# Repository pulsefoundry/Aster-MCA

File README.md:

# Aster MCA

[简体中文](README.zh-CN.md)

Aster MCA is a compact, USB-powered 4096-channel pulse-height analyzer for
already-amplified detector signals. It combines a 12-bit 10 MSPS ADC, a Gowin
GW1N-4 FPGA, and a CH347T USB/JTAG/UART bridge on one 90 mm × 70 mm four-layer
board.

> **Prototype status:** revision 0.1 has acquired a repeatable Cs-137 spectrum
> from an amplified NaI(Tl)/PMT probe, but the published as-built hardware has
> three mandatory assembly notes. Do not order or assemble the v0.1 production
> package unchanged. See [Hardware errata](docs/hardware-errata-v0.1.md).

*Assembled and physically validated v0.1 prototype.*

## What works

- ADC12010 parallel capture at 10 MSPS.
- FPGA baseline tracking, threshold detection, peak-height extraction, pulse
  rejection, saturation recovery, and a 4096 × 32-bit histogram.
- USB communication on macOS through the on-board CH347T and libusb; no serial
  driver or external programmer is required.
- Volatile SRAM configuration over the same USB-C connector.
- Live diagnostics for ADC min/max/baseline, triggers, accepted/rejected and
  saturated events, histogram drops, live samples, and UART errors.
- Repeatable source-versus-background separation on the first repaired boards.

The current physically validated firmware is **v1.9**. It keeps the proven v1.3
MCA algorithm but moves all 12 ADC inputs into dedicated falling-edge IOLOGIC
registers, followed by a full-cycle fabric pipeline stage. Two independently
placed images now produce matching Cs-137 spectra. FPGA configuration is
volatile and must be reloaded after power loss.

## Aster MCA v2.0 concept

The repository also contains a routed, explicitly unreleased
[v2.0 high-performance concept](hardware/rev2.0-preliminary/README.md): a
16-bit 40 MSPS ADS5560, Intel MAX 10 FPGA, directly soldered RP2350 host module,
and three fixed analogue ranges of approximately 0.5x, 5x and 25x. The current
r8 CAD passes ERC, DRC and an independent 489-pin network audit, and its THS4551
front end has reproducible analogue simulations.

v2.0 has no FPGA firmware or physical prototype yet. Its manufacturing files
are published for review and quotation only and must not be treated as a
production release.

## Prototype photographs

| Powered bench prototype | Second PCB during assembly and inspection |
| --- | --- |
|  |  |

The full bench setup shows the amplified NaI(Tl)/PMT probe, oscilloscope,
Aster MCA prototype, and host computer during the initial Cs-137 validation.
The spectrum window in this photograph still carries the pre-release working
name used before the project was renamed Aster MCA.

## Measured prototype result

The initial validation used an amplified 1-inch NaI(Tl)/PMT probe and a Cs-137
check source. The analog stage was set to approximately ×3.33, the trigger
threshold was 32 ADC codes, and negative-going pulses were selected.

| Quantity | Result |
| --- | ---: |
| Source live time | 943.493 s |
| Source count rate | 252.19 counts/s |
| Background count rate | 77.72 counts/s |
| Net source rate | 174.47 counts/s |
| 662 keV peak position | about channel 95.8 |
| Preliminary FWHM | about 11.0 channels |
| Preliminary resolution | about 11.5% |
| Histogram drops | 0 |

These numbers describe one prototype setup, not a guaranteed instrument
specification. The energy estimate is based on a single known line, a short
background run, and a simple local-continuum subtraction. Raw CSV files are in
[`examples/cs137`](examples/cs137/).

## Analog gain options

R62/R63 are the matched 1.00 kohm `RG` pair and R64/R65 are the fitted matched
10.0 kohm `RF` pair. R66 and R67 are optional **parallel** feedback positions:
leave both open for nominal gain ×10, or fit the same value on both sides to
reduce the gain. The measured Cs-137 setup used 4.99 kohm, 0.1% at both R66 and
R67, giving `10k || 4.99k ≈ 3.33k` and nominal gain about ×3.33. Never populate
only one of the pair. See [Analog gain configuration](docs/gain-configuration.md)
for the formula, component roles, and calibration consequences.

## Signal path

```text
conditioned detector pulse
        │
        ▼
AC coupling and bias ──► AD8137 differential driver
        │
        ▼
ADC12010, 12 bit / 10 MSPS ──► GW1N-4 FPGA
        │                          │
        │                          ├─ baseline and peak extraction
        │                          └─ 4096-bin histogram
        ▼
CH347T USB UART/JTAG ──► macOS host utility
```

The BNC input is **low-voltage and signal-only**. The board has no detector
high-voltage supply, no high-voltage blocking network, and no charge-sensitive
preamplifier. Never connect a PMT bias line, a bare photomultiplier, or a
high-voltage detector cable directly to the input.

## Complete schematic

The image above combines all five sheets of the as-built v0.1 schematic; click
it to open the original full-resolution PDF. It documents the manufactured
prototype and therefore includes the known U8, S1, and U6 assembly notes. Read
the [hardware errata](docs/hardware-errata-v0.1.md) before fabrication.

## Repository layout

- `hardware/rev0.1-as-built/` — EasyEDA Pro source, Gerbers, BOM, CPL,
  schematic, netlist, and pin/net reference for the manufactured prototype.
- `firmware/mca-v1/` — synthesizable Verilog, constraints, simulations, host
  utility, tests, and validated v1.3 and v1.9 SRAM images.
- `docs/` — bring-up procedure, protocol, hardware errata, and validation
  notes.
- `examples/cs137/` — raw spectrum and background CSV files.

## Fabrication archive

The complete v0.1 as-built package is available as
[`Aster-MCA-v0.1-as-built-production.zip`](release/Aster-MCA-v0.1-as-built-production.zip).
It contains the native EasyEDA Pro project, Gerbers, BOM, CPL, schematic,
netlist, pin/net reference, assembly overrides, and hardware licence. This is
the manufactured prototype archive, not a corrected production release: read
the included notice and [v0.1 errata](docs/hardware-errata-v0.1.md) first.

## Quick start with an existing repaired board

Requirements on macOS:

```sh
brew install libusb openfpgaloader iverilog
```

Load the tested prebuilt image into FPGA SRAM:

```sh
cd firmware/mca-v1
openFPGALoader -c ch347_jtag --freq 1000000 -m \
  prebuilt/aster-mca-v1.9.fs
```

The original v1.3 image remains available as a fallback. See
[Algorithm development](docs/algorithm-development.en.md) for the ADC capture
fault, physical placement-seed test, and the rules for future algorithm A/B
comparisons.

Read the board and acquire a spectrum:

```sh
python3 astermca.py info
python3 astermca.py stats
python3 astermca.py acquire 600 --threshold 32 -o spectrum.csv
```

For a first power-up, follow [`docs/bring-up.md`](docs/bring-up.md) rather than
connecting a detector immediately.

## Build and test

The FPGA build uses Yosys, nextpnr-himbaechel, `gowin_pack`, Icarus Verilog,
and openFPGALoader. The easiest route is an OSS CAD Suite release with its
`bin` directory on `PATH`.

```sh
cd firmware/mca-v1
make sim
make host-test
make
make detect
make load-sram
```

You can instead pass an OSS CAD Suite binary directory explicitly:

```sh
make TOOLBIN=/absolute/path/to/oss-cad-suite/bin
```

## Hardware revision warning

Revision 0.1 is published for transparency and reproducibility, not as a
drop-in production release:

1. **U8:** the released BOM specifies `LMV321IDBVR`, but the PCB net map expects
   the pin order of `MCP6001T-I/OT`. Fit the plain MCP6001T-I/OT variant or
   apply the documented bypass. Do not fit MCP6001R or MCP6001U.
2. **S1:** leave the reset switch unpopulated. The footprint contact pairing
   can hold `RECONFIG_N` low on the assembled board.
3. **U6:** the originally specified `SGM2037-1.2XN5G/TR` remains recommended
   for a new build. The substitute `AP2112K-1.2` was later verified to start
   successfully without added output capacitance. Extra parallel output
   capacitance is not normally required; consider it only if oscilloscope
   measurements confirm that an excessively fast +1V2 rise causes FPGA
   configuration or startup failure, then re-check regulator stability,
   overshoot, and repeatable FPGA configuration.

Read the full [v0.1 errata and recovery procedure](docs/hardware-errata-v0.1.md)
before using the fabrication files.

## Contributing

Bug reports, measurements from other detector/front-end combinations, host
support for additional operating systems, HDL review, and a corrected hardware
revision are welcome. See [CONTRIBUTING.md](CONTRIBUTING.md).

## AI-assisted development

The FPGA firmware, HDL tests, Python host utility, and parts of the technical
documentation were developed with assistance from OpenAI Codex/ChatGPT. The
release was subsequently checked by simulation, synthesis/place-and-route,
timing analysis, and operation on the physical prototype. See the full
[AI development disclosure](AI-DISCLOSURE.md).

## License

Hardware design files are licensed under CERN-OHL-P-2.0. Firmware, host
software, documentation, tests, images, and example data are licensed under
MIT. See [LICENSE.md](LICENSE.md) for the exact scope and full licence texts.

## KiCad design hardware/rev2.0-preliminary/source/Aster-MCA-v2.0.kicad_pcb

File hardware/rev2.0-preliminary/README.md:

# Aster MCA v2.0 high-performance concept

This directory publishes the current **r8 engineering design** for a higher-
performance Aster MCA. It is a routed, auditable hardware concept, not a
released production design.

> **Do not order this revision as a finished instrument.** The schematic and
> PCB are internally consistent, but there is no MAX 10 firmware or physical
> prototype yet. Read [PRODUCTION-NOTICE.md](PRODUCTION-NOTICE.md) first.

## Design direction

| Block | Current r8 choice |
| --- | --- |
| ADC | TI ADS5560, 16 bit, 40 MSPS, parallel CMOS output |
| FPGA | Intel MAX 10 10M16SAE144C8G, internal configuration flash, no external DDR |
| Host | Direct-soldered 52 mm x 21 mm RP2350/Pico 2-compatible castellated module |
| Analogue driver | TI THS4551 fully differential amplifier |
| Input ranges | Nominal 0.5x, 5x and 25x selected by a board-edge DP3T switch |
| Board | 90 mm x 70 mm, four layers, solid internal ground plane |
| User interface | Board-edge reset/reconfigure switch and four 3 mm through-hole LEDs |

The FPGA is intended to capture the complete 16-bit ADC bus and perform
triggering, baseline tracking, pulse-height/area extraction, pile-up handling,
histogramming and event buffering. The RP2350 module is intended to provide
USB, configuration, control and higher-level data transfer. Firmware for this
architecture has not yet been implemented.

## Three-range front end

The present resistor network provides three repeatable fixed ranges rather
than a dual potentiometer whose channel tracking and wiper noise would be hard
to calibrate:

| Range | Signal-side nominal gain | Intended use |
| --- | ---: | --- |
| Low | 0.5002x | Bring-up and occasional multi-volt detector pulses |
| Medium | 4.9665x | General spectroscopy range |
| High | 25.413x | Weak and low-energy pulses |

The reference-side gains are 0.5000x, 4.9751x and 25.413x. These are circuit
ratios for negligible detector source impedance, not energy-calibration
constants. Every assembled range requires pulse-injection and source
calibration. The 25x range is not presently qualified for multi-volt overload;
begin first power-up on 0.5x.

See [GAIN-OPTIMIZATION-r7.md](reference/GAIN-OPTIMIZATION-r7.md) for the exact
network and safety limits.

## Analogue simulation and r8 correction

The THS4551 front end was exercised with TI's PSpice macro-model. The original
10 ohm ADC isolation resistors showed a 9.74 dB simulated resonance near
35.5 MHz with the present 2.2 nF differential capacitor. r8 changes both
resistors to 22 ohm. The rerun produced approximately 1.56-1.65 MHz bandwidth,
less than 0.46 us simulated 1% settling, and no observed AC peaking in all
three ranges.

This model does not reproduce the ADS5560 switched-capacitor input, so the
result is a design check rather than a substitute for oscilloscope validation.
See [DAMPING-FIX-r8.md](reference/DAMPING-FIX-r8.md) and the reproducible files
under [`simulation/r7/`](simulation/r7/).

## Current verification status

Fresh checks against the r8 editable source on 2026-09-26 report:

- schematic ERC: 0 errors and 0 warnings;
- PCB DRC: 0 violations, 0 unconnected pads and 0 footprint errors;
- 111/111 manifest references present;
- all 489 numbered pad/net assignments match the independent manifest;
- critical FPGA/ADC clock, THS4551, AP63203, gain-switch and ADC-input networks
  pass the static audit;
- all four copper layers are present, with In1.Cu reserved as the solid ground
  plane.

These checks prove CAD consistency, not physical operation.

## Remaining release gates

1. Build and compile an exact `10M16SAE144C8G` Quartus project, proving package
   pin legality, ADC timing and the RP2350 interface.
2. Overlay the exact purchased 52 mm x 21 mm RP2350 clone on a 1:1 print and
   verify every castellated contact and USB overhang.
3. Verify the purchased JS203011AQN switch continuity and physical slider
   order before printing enclosure labels.
4. Bind every fitted BOM line to an exact purchasable part and recheck stock.
5. On a prototype, measure all rails, total USB current, ADC clock/data timing,
   front-end settling, overload recovery and range gain.
6. Repeat native EasyEDA/JLCPCB DRC, paste, rotation and 3D review before any
   assembly order.

## Files worth reviewing

- `source/Aster-MCA-v2.0.kicad_sch` and `.kicad_pcb` — current editable r8
  design and routing authority;
- `source/footprints/` — project-local production footprints;
- `reference/Aster-MCA-v2.0-schematic.pdf` — rendered schematic;
- `reference/parts-manifest.json` and `netlist-pin-map.csv` — independent
  connectivity references;
- `reference/quartus-pin-assignment-preliminary.csv` — preliminary MAX 10
  signal assignments, still requiring compilation;
- `production/quote-r8-current-source/` — quote-only Gerbers, BOM and CPL;
- `simulation/r7/` — analogue simulation and static-audit scripts and results.

The quote package is deliberately labelled **QUOTE ONLY**. It exists to study
cost and assembly options; it is not a production release.

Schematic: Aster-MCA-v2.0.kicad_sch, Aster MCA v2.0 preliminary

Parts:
A1: RP2350 Pico 2 compatible 52x21mm; RP2350_Clone_52x21mm_Castellated
C1: 100n FILM DNP; Capacitor_THT__C_Rect_L7.2mm_W2.5mm_P5.00mm__AsterProd; not fitted
C2: 2.2n C0G; Capacitor_SMD__C_0603_1608Metric__AsterProd
C5, C7, C9, C10, C11, C12, C13, C14, C15, C16, C17, C18, C19, C20, C21, C22, C23, C24, C30, C31, C32, C33, C34, C35, C36, C37, C42: 100n; Capacitor_SMD__C_0603_1608Metric__AsterProd
C6: 2.2u; Capacitor_SMD__C_0805_2012Metric_Pad1.18x1.45mm_HandSolder_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
C8: 1u; Capacitor_SMD__C_0805_2012Metric_Pad1.18x1.45mm_HandSolder_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
C25, C26, C27, C29: 4.7u; Capacitor_SMD__C_0805_2012Metric_Pad1.18x1.45mm_HandSolder_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
C28: 10u; Capacitor_SMD__C_0805_2012Metric_Pad1.18x1.45mm_HandSolder_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
C38: 100n; Capacitor_SMD__C_0402_1005Metric__AsterProd
C39: 10u 10V; Capacitor_SMD__C_1206_3216Metric_Pad1.33x1.80mm_HandSolder_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
C40, C41: 22u 6.3V; Capacitor_SMD__C_1206_3216Metric_Pad1.33x1.80mm_HandSolder_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
D1: PESD5V0S1UL DNP; Diode_SMD__D_SOD-323_HandSoldering__AsterProd; not fitted
D2: PWR; LED_THT__LED_D3.0mm__AsterProd
D3: RUN; LED_THT__LED_D3.0mm__AsterProd
D4: TRIG; LED_THT__LED_D3.0mm__AsterProd
D5: SAT; LED_THT__LED_D3.0mm__AsterProd
D6: SS14L USB OR; Diode_SMD__D_SOD-123F__AsterProd
D7: SS14L EXT OR; Diode_SMD__D_SOD-123F__AsterProd
F1: 1.5A RESETTABLE; Fuse__Fuse_1206_3216Metric_Pad1.42x1.75mm_HandSolder__Aster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
FB1, FB2, FB3, FB4: 600R@100MHz 1A; Inductor_SMD__L_0805_2012Metric_Pad1.05x1.20mm_HandSolder__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
J1: BNC INPUT; Connector_Coaxial__BNC_Amphenol_031-5539_Vertical__AsterProd
J2: INTEL JTAG; Connector_PinHeader_2.54mm__PinHeader_2x05_P2.54mm_Vertical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
J3: EXT TRIG; Connector_PinHeader_2.54mm__PinHeader_1x03_P2.54mm_Vertical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
J4: ALT 5V IN; Connector_PinHeader_2.54mm__PinHeader_1x02_P2.54mm_Vertical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
JP1: 50R TERM; Connector_PinHeader_2.54mm__PinHeader_1x02_P2.54mm_Vertical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
JP2: DC / AC; Connector_PinHeader_2.54mm__PinHeader_1x03_P2.54mm_Vertical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
L1: 3.9uH >=3A; Inductor_SMD__L_Changjiang_FNR6020S__AsterProd
R1: 49R9 0.1% DNP; Resistor_SMD__R_0805_2012Metric_Pad1.20x1.40mm_HandSolder__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; not fitted
R2, R4: 78R7 0.1%; Resistor_SMD__R_0805_2012Metric_Pad1.20x1.40mm_HandSolder__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
R3: 0R; Resistor_SMD__R_0805_2012Metric_Pad1.20x1.40mm_HandSolder__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
R5: 3k92 0.1%; Resistor_SMD__R_0805_2012Metric_Pad1.20x1.40mm_HandSolder__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
R6: 4k00 0.1%; Resistor_SMD__R_0805_2012Metric_Pad1.20x1.40mm_HandSolder__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
R7, R8: 2k00 0.1%; Resistor_SMD__R_0805_2012Metric_Pad1.20x1.40mm_HandSolder__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
R9, R10: 22R 1%; Resistor_SMD__R_0805_2012Metric__AsterProd
R11, R14, R33, R34, R35, R37, R38, R39, R40, R41: 10k; Resistor_SMD__R_0805_2012Metric_Pad1.20x1.40mm_HandSolder__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
R12: 8k25 1%; Resistor_SMD__R_0805_2012Metric_Pad1.20x1.40mm_HandSolder__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
R13: 4k99 1%; Resistor_SMD__R_0805_2012Metric_Pad1.20x1.40mm_HandSolder__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
R15, R16: 33R; Resistor_SMD__R_0805_2012Metric_Pad1.20x1.40mm_HandSolder__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
R36, R42, R43, R44, R45: 1k; Resistor_SMD__R_0805_2012Metric_Pad1.20x1.40mm_HandSolder__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
R46: 324R 0.1%; Resistor_SMD__R_0805_2012Metric_Pad1.20x1.40mm_HandSolder__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
R47: 402R 0.1%; Resistor_SMD__R_0805_2012Metric_Pad1.20x1.40mm_HandSolder__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
RN1, RN2, RN3, RN4: 33R x4 isolated; Resistor_SMD__R_Array_Convex_4x0603__AsterProd
SW1: GAIN 0.5x / 5x / 25x; Button_Switch_THT__SW_CK_JS203011AQN_DP3T_Angled__AsterProd
SW2: FPGA RECONFIG; Button_Switch_THT__SW_Tactile_SPST_Angled_PTS645Vx39-2LFS__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
TP1: TP_GND; TestPoint__TestPoint_Plated_Hole_D2.0mm__AsterProd
TP2: TP_5V; TestPoint__TestPoint_Plated_Hole_D2.0mm__AsterProd
TP3: TP_3V3D; TestPoint__TestPoint_Plated_Hole_D2.0mm__AsterProd
TP4: TP_3V3A; TestPoint__TestPoint_Plated_Hole_D2.0mm__AsterProd
TP5: TP_VCM; TestPoint__TestPoint_Plated_Hole_D2.0mm__AsterProd
U1: 10M16SAE144C8G; Package_QFP__EQFP-144-1EP_20x20mm_P0.5mm_EP4x4mm__AsterProd
U2: ADS5560IRGZT; Package_DFN_QFN__Texas_RGZ0048A_VQFN-48-1EP_7x7mm_P0.5mm_EP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
U3: THS4551IDGKT; Package_SO__VSSOP-8_3x3mm_P0.65mm__AsterProd
U4: AP63203WU-7; Package_TO_SOT_SMD__TSOT-23-6_HandSoldering__AsterProd
Y1: 40.000 MHz CMOS; Oscillator__Oscillator_SMD_Abracon_ASE-4Pin_3.2x2.5mm_HandS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

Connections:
3V3_A: C28.1 (3V3_A), C30.1 (3V3_A), C32.1 (3V3_A), C33.1 (3V3_A), C34.1 (3V3_A), C35.1 (3V3_A), FB2.2 (3V3_A), TP4.1, U2.8 (3V3_A), U2.18 (3V3_A), U2.20 (3V3_A), U2.22 (3V3_A), U2.24 (3V3_A), U2.26 (3V3_A)
3V3_D: C11.1 (3V3_D), C12.1 (3V3_D), C13.1 (3V3_D), C14.1 (3V3_D), C15.1 (3V3_D), C16.1 (3V3_D), C17.1 (3V3_D), C18.1 (3V3_D), C19.1 (3V3_D), C20.1 (3V3_D), C25.1 (3V3_D), C27.1 (3V3_D), C29.1 (3V3_D), C31.1 (3V3_D), C36.1 (3V3_D), C37.1 (3V3_D), C42.1 (3V3_D), D2.2 (3V3_D), FB1.2 (3V3_D), J2.4 (3V3_D), J3.1 (3V3_D), R12.1 (3V3_D), R14.1 (3V3_D), R33.1 (3V3_D), R34.1 (3V3_D), R35.1 (3V3_D), R37.1 (3V3_D), R38.1 (3V3_D), R39.1 (3V3_D), R40.1 (3V3_D), R41.1 (3V3_D), TP3.1, U1.9 (3V3_D), U1.23 (3V3_D), U1.31 (3V3_D), U1.40 (3V3_D), U1.49 (3V3_D), U1.67 (3V3_D), U1.82 (3V3_D), U1.94 (3V3_D), U1.103 (3V3_D), U1.117 (3V3_D), U1.128 (3V3_D), U1.139 (3V3_D), U2.2 (3V3_D), U2.7 (3V3_D), U2.27 (3V3_D), U2.30 (3V3_D), U2.35 (3V3_D), Y1.4 (3V3_D)
3V3_FPGA_A: C21.1 (3V3_FPGA_A), C22.1 (3V3_FPGA_A), C23.1 (3V3_FPGA_A), C24.1 (3V3_FPGA_A), C26.1 (3V3_FPGA_A), FB3.2 (3V3_FPGA_A), U1.1 (3V3_FPGA_A), U1.2 (3V3_FPGA_A), U1.34 (3V3_FPGA_A), U1.35 (3V3_FPGA_A), U1.36 (3V3_FPGA_A), U1.37 (3V3_FPGA_A), U1.51 (3V3_FPGA_A), U1.71 (3V3_FPGA_A), U1.72 (3V3_FPGA_A), U1.73 (3V3_FPGA_A), U1.107 (3V3_FPGA_A), U1.108 (3V3_FPGA_A), U1.109 (3V3_FPGA_A), U1.115 (3V3_FPGA_A), U1.143 (3V3_FPGA_A), U1.144 (3V3_FPGA_A)
3V3_RAW: C40.1 (3V3_RAW), C41.1 (3V3_RAW), FB1.1 (3V3_RAW), FB2.1 (3V3_RAW), FB3.1 (3V3_RAW), L1.2 (3V3_RAW), U4.1 (3V3_RAW)
5VA: C5.1 (5VA), C6.1 (5VA), FB4.2 (5VA), R11.1 (5VA), U3.3 (5VA)
5V_FUSED: C39.1 (5V_FUSED), D6.1 (5V_FUSED), D7.1 (5V_FUSED), FB4.1 (5V_FUSED), TP2.1, U4.2 (5V_FUSED), U4.3 (5V_FUSED)
ADC_CLKM: C9.1 (ADC_CLKM), U2.11 (ADC_CLKM)
ADC_CLKOUT: R16.1 (ADC_CLKOUT), U2.5 (ADC_CLKOUT)
ADC_CLKP: C10.2 (ADC_CLKP), U2.10 (ADC_CLKP)
ADC_D0: RN4.4 (ADC_D0), U2.31 (ADC_D0)
ADC_D1: RN4.3 (ADC_D1), U2.32 (ADC_D1)
ADC_D2: RN4.2 (ADC_D2), U2.33 (ADC_D2)
ADC_D3: RN4.1 (ADC_D3), U2.34 (ADC_D3)
ADC_D4: RN3.4 (ADC_D4), U2.37 (ADC_D4)
ADC_D5: RN3.3 (ADC_D5), U2.38 (ADC_D5)
ADC_D6: RN3.2 (ADC_D6), U2.39 (ADC_D6)
ADC_D7: RN3.1 (ADC_D7), U2.40 (ADC_D7)
ADC_D8: RN2.4 (ADC_D8), U2.41 (ADC_D8)
ADC_D9: RN2.3 (ADC_D9), U2.42 (ADC_D9)
ADC_D10: RN2.2 (ADC_D10), U2.43 (ADC_D10)
ADC_D11: RN2.1 (ADC_D11), U2.44 (ADC_D11)
ADC_D12: RN1.4 (ADC_D12), U2.45 (ADC_D12)
ADC_D13: RN1.3 (ADC_D13), U2.46 (ADC_D13)
ADC_D14: RN1.2 (ADC_D14), U2.47 (ADC_D14)
ADC_D15: RN1.1 (ADC_D15), U2.48 (ADC_D15)
ADC_DFS: R12.2 (ADC_DFS), R13.1 (ADC_DFS), U2.6 (ADC_DFS)
ADC_INM: C2.2 (ADC_INM), R9.2 (ADC_INM), U2.16 (ADC_INM)
ADC_INP: C2.1 (ADC_INP), R10.2 (ADC_INP), U2.15 (ADC_INP)
ADC_OVR: U1.69 (ADC_OVR), U2.3 (ADC_OVR)
ADC_VCM: C7.1 (ADC_VCM), C8.1 (ADC_VCM), TP5.1, U2.13 (ADC_VCM), U3.2 (ADC_VCM)
AFE_AC: C1.2 (AFE_AC), JP2.3 (AFE_AC)
AFE_IN: C1.1 (AFE_IN), D1.2 (AFE_IN), JP2.1 (AFE_IN), R2.2 (AFE_IN)
ALT_5V_IN: D7.2 (ALT_5V_IN), J4.1 (ALT_5V_IN)
BUCK_BST: C38.1 (BUCK_BST), U4.6 (BUCK_BST)
BUCK_SW: C38.2 (BUCK_SW), L1.1 (BUCK_SW), U4.5 (BUCK_SW)
CLK40_RAW: C10.1 (CLK40_RAW), R15.1 (CLK40_RAW), Y1.3 (CLK40_RAW)
CLK_OE: R14.2 (CLK_OE), Y1.1 (CLK_OE)
CONF_DONE: R39.2 (CONF_DONE), U1.138 (CONF_DONE)
EXT_TRIG: A1.22 (EXT_TRIG), J3.2 (EXT_TRIG), R41.2 (EXT_TRIG), U1.93 (EXT_TRIG)
FDA_INN: R3.2 (FDA_INN), R5.2 (FDA_INN), R7.2 (FDA_INN), R46.2 (FDA_INN), U3.1 (FDA_INN)
FDA_INP: R4.2 (FDA_INP), R6.2 (FDA_INP), R8.2 (FDA_INP), R47.2 (FDA_INP), U3.8 (FDA_INP)
FDA_OUTN: R8.1 (FDA_OUTN), R10.1 (FDA_OUTN), U3.5 (FDA_OUTN)
FDA_OUTP: R7.1 (FDA_OUTP), R9.1 (FDA_OUTP), U3.4 (FDA_OUTP)
FDA_PD: R11.2 (FDA_PD), U3.7 (FDA_PD)
FPGA_ADCCLK: R16.2 (FPGA_ADCCLK), U1.58 (FPGA_ADCCLK)
FPGA_ADC_D0: RN4.5 (FPGA_ADC_D0), U1.62 (FPGA_ADC_D0)
FPGA_ADC_D1: RN4.6 (FPGA_ADC_D1), U1.61 (FPGA_ADC_D1)
FPGA_ADC_D2: RN4.7 (FPGA_ADC_D2), U1.60 (FPGA_ADC_D2)
FPGA_ADC_D3: RN4.8 (FPGA_ADC_D3), U1.59 (FPGA_ADC_D3)
FPGA_ADC_D4: RN3.5 (FPGA_ADC_D4), U1.64 (FPGA_ADC_D4)
FPGA_ADC_D5: RN3.6 (FPGA_ADC_D5), U1.54 (FPGA_ADC_D5)
FPGA_ADC_D6: RN3.7 (FPGA_ADC_D6), U1.52 (FPGA_ADC_D6)
FPGA_ADC_D7: RN3.8 (FPGA_ADC_D7), U1.50 (FPGA_ADC_D7)
FPGA_ADC_D8: RN2.5 (FPGA_ADC_D8), U1.47 (FPGA_ADC_D8)
FPGA_ADC_D9: RN2.6 (FPGA_ADC_D9), U1.46 (FPGA_ADC_D9)
FPGA_ADC_D10: RN2.7 (FPGA_ADC_D10), U1.45 (FPGA_ADC_D10)
FPGA_ADC_D11: RN2.8 (FPGA_ADC_D11), U1.44 (FPGA_ADC_D11)
FPGA_ADC_D12: RN1.5 (FPGA_ADC_D12), U1.43 (FPGA_ADC_D12)
FPGA_ADC_D13: RN1.6 (FPGA_ADC_D13), U1.41 (FPGA_ADC_D13)
FPGA_ADC_D14: RN1.7 (FPGA_ADC_D14), U1.39 (FPGA_ADC_D14)
FPGA_ADC_D15: RN1.8 (FPGA_ADC_D15), U1.38 (FPGA_ADC_D15)
FPGA_REFCLK: R15.2 (FPGA_REFCLK), U1.56 (FPGA_REFCLK)
FPGA_RESET_N: A1.21 (FPGA_RESET_N), R40.2 (FPGA_RESET_N), U1.92 (FPGA_RESET_N)
FPGA_RUN: D3.2 (FPGA_RUN), U1.110 (FPGA_RUN)
FPGA_SAT: D5.2 (FPGA_SAT), U1.120 (FPGA_SAT)
FPGA_TRIG: D4.2 (FPGA_TRIG), U1.111 (FPGA_TRIG)
GAIN_H_GND: R4.1 (GAIN_H_GND), SW1.5 (GAIN_H_GND)
GAIN_H_SIG: R3.1 (GAIN_H_SIG), SW1.1 (GAIN_H_SIG)
GAIN_L_GND: R6.1 (GAIN_L_GND), SW1.8 (GAIN_L_GND)
GAIN_L_SIG: R5.1 (GAIN_L_SIG), SW1.4 (GAIN_L_SIG)
GAIN_M_GND: R47.1 (GAIN_M_GND), SW1.6 (GAIN_M_GND)
GAIN_M_SIG: R46.1 (GAIN_M_SIG), SW1.2 (GAIN_M_SIG)
GAIN_SRC: JP2.2 (GAIN_SRC), SW1.3 (GAIN_SRC)
GND: A1.3 (GND), A1.8 (GND), A1.13 (GND), A1.18 (GND), A1.23 (GND), A1.28 (GND), A1.33 (GND), A1.38 (GND), C5.2 (GND), C6.2 (GND), C7.2 (GND), C8.2 (GND), C9.2 (GND), C11.2 (GND), C12.2 (GND), C13.2 (GND), C14.2 (GND), C15.2 (GND), C16.2 (GND), C17.2 (GND), C18.2 (GND), C19.2 (GND), C20.2 (GND), C21.2 (GND), C22.2 (GND), C23.2 (GND), C24.2 (GND), C25.2 (GND), C26.2 (GND), C27.2 (GND), C28.2 (GND), C29.2 (GND), C30.2 (GND), C31.2 (GND), C32.2 (GND), C33.2 (GND), C34.2 (GND), C35.2 (GND), C36.2 (GND), C37.2 (GND), C39.2 (GND), C40.2 (GND), C41.2 (GND), C42.2 (GND), D1.1 (GND), J1.2 (GND), J2.2 (GND), J2.10 (GND), J3.3 (GND), J4.2 (GND), R1.2 (GND), R13.2 (GND), R36.2 (GND), R42.1 (GND), R43.1 (GND), R44.1 (GND), R45.1 (GND), SW1.7 (GND), SW2.2 (GND), TP1.1, U1.3 (GND), U1.4 (GND), U1.42 (GND), U1.53 (GND), U1.63 (GND), U1.68 (GND), U1.83 (GND), U1.95 (GND), U1.104 (GND), U1.116 (GND), U1.125 (GND), U1.133 (GND), U1.137 (GND), U1.142 (GND), U1.145 (GND), U2.1 (GND), U2.9 (GND), U2.12 (GND), U2.14 (GND), U2.17 (GND), U2.19 (GND), U2.23 (GND), U2.25 (GND), U2.28 (GND), U2.29 (GND), U2.36 (GND), U2.49 (GND), U3.6 (GND), U4.4 (GND), Y1.2 (GND)
HOST_AUX: A1.20 (HOST_AUX), U1.91 (HOST_AUX)
HOST_CS: A1.14 (HOST_CS), U1.86 (HOST_CS)
HOST_D0: A1.1 (HOST_D0), U1.81 (HOST_D0)
HOST_D1: A1.2 (HOST_D1), U1.80 (HOST_D1)
HOST_D2: A1.4 (HOST_D2), U1.79 (HOST_D2)
HOST_D3: A1.5 (HOST_D3), U1.78 (HOST_D3)
HOST_D4: A1.6 (HOST_D4), U1.77 (HOST_D4)
HOST_D5: A1.7 (HOST_D5), U1.76 (HOST_D5)
HOST_D6: A1.9 (HOST_D6), U1.75 (HOST_D6)
HOST_D7: A1.10 (HOST_D7), U1.74 (HOST_D7)
HOST_IRQ: A1.15 (HOST_IRQ), U1.87 (HOST_IRQ)
HOST_MISO: A1.19 (HOST_MISO), U1.90 (HOST_MISO)
HOST_MOSI: A1.17 (HOST_MOSI), U1.89 (HOST_MOSI)
HOST_RD: A1.12 (HOST_RD), U1.85 (HOST_RD)
HOST_SCK: A1.16 (HOST_SCK), U1.88 (HOST_SCK)
HOST_WR: A1.11 (HOST_WR), U1.84 (HOST_WR)
JTAGEN: R33.2 (JTAGEN), U1.15 (JTAGEN)
JTAG_TCK: J2.1 (JTAG_TCK), R36.1 (JTAG_TCK), U1.18 (JTAG_TCK)
JTAG_TDI: J2.9 (JTAG_TDI), R35.2 (JTAG_TDI), U1.19 (JTAG_TDI)
JTAG_TDO: J2.3 (JTAG_TDO), U1.20 (JTAG_TDO)
JTAG_TMS: J2.5 (JTAG_TMS), R34.2 (JTAG_TMS), U1.16 (JTAG_TMS)
LED_R1: D2.1 (LED_R1), R42.2 (LED_R1)
LED_R2: D3.1 (LED_R2), R43.2 (LED_R2)
LED_R3: D4.1 (LED_R3), R44.2 (LED_R3)
LED_R4: D5.1 (LED_R4), R45.2 (LED_R4)
NCONFIG: R37.2 (NCONFIG), SW2.1 (NCONFIG), U1.129 (NCONFIG)
NSTATUS: R38.2 (NSTATUS), U1.136 (NSTATUS)
PMT_IN: J1.1 (PMT_IN), JP1.1 (PMT_IN), R2.1 (PMT_IN)
TERM_50: JP1.2 (TERM_50), R1.1 (TERM_50)
USB_5V_PROTECTED: D6.2 (USB_5V_PROTECTED), F1.2 (USB_5V_PROTECTED)
VBUS: A1.40 (VBUS), F1.1 (VBUS)

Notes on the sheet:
ASTER MCA v2.0 — 16-bit / 40 MSPS / MAX 10 / RP2350
PRELIMINARY ENGINEERING SCHEMATIC — NOT RELEASED FOR FABRICATION
Analog gain: LOW ≈0.5x, HIGH ≈20x; both halves of SW1 change together.
ANALOG INPUT / GAIN / ADC SUPPORT
FPGA / HOST SUPPORT
POWER
TEST POINTS

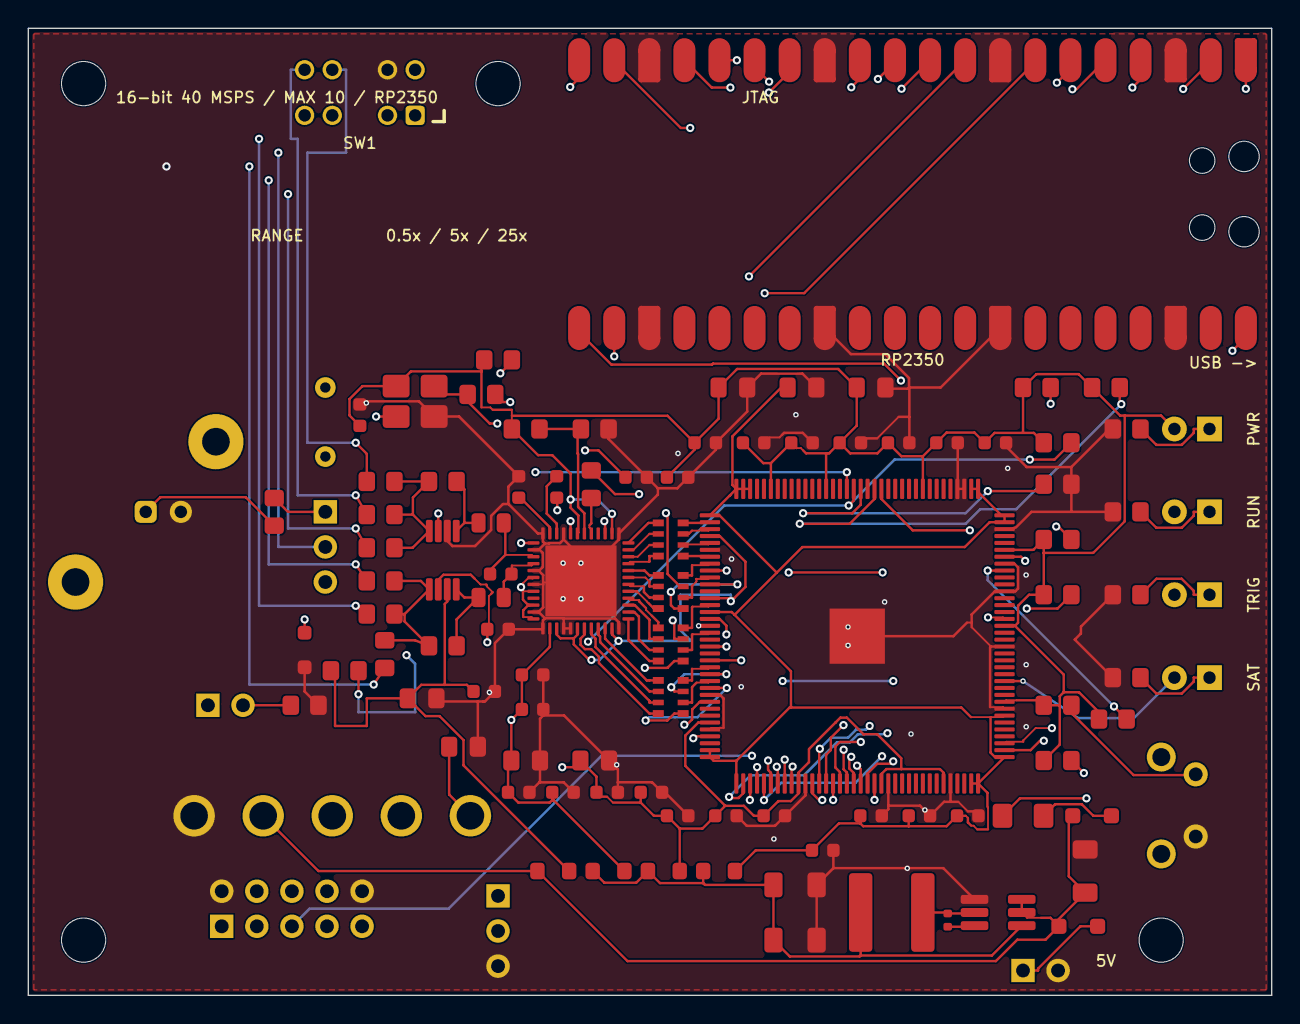
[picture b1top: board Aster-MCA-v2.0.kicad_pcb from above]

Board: 4 copper layers, 90.0 x 70.0 mm, 111 parts (0 on the bottom side), 105 nets.

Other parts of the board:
H1, H2, H3, H4: MountingHole_3.2mm_M3; __MountingHole_3.2mm_M3__AsterProd

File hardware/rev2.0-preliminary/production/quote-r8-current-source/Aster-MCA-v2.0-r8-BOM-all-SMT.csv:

Comment,Designator,Footprint,LCSC Part #,Manufacturer Part Number,Qty
100n,"C10,C11,C12,C13,C14,C15,C16,C17,C18,C19,C20,C21,C22,C23,C24,C30,C31,C32,C33,C34,C35,C36,C37,C42,C5,C7,C9",Capacitor_SMD:C_0603_1608Metric,C1853266,CC0603KPX7R8BB104,27
2.2n C0G,C2,Capacitor_SMD:C_0603_1608Metric,C343869,GCM1885C1H222JA16D,1
4.7u,"C25,C26,C27,C29",Capacitor_SMD:C_0805_2012Metric_Pad1.18x1.45mm_HandSolder,,,4
10u,C28,Capacitor_SMD:C_0805_2012Metric_Pad1.18x1.45mm_HandSolder,,,1
100n,C38,Capacitor_SMD:C_0402_1005Metric,C1525,CL05B104KO5NNNC,1
10u 10V,C39,Capacitor_SMD:C_1206_3216Metric_Pad1.33x1.80mm_HandSolder,,,1
22u 6.3V,"C40,C41",Capacitor_SMD:C_1206_3216Metric_Pad1.33x1.80mm_HandSolder,,,2
2.2u,C6,Capacitor_SMD:C_0805_2012Metric_Pad1.18x1.45mm_HandSolder,,,1
1u,C8,Capacitor_SMD:C_0805_2012Metric_Pad1.18x1.45mm_HandSolder,,,1
SS14L USB OR,D6,Diode_SMD:D_SOD-123F,C190475,SS14L,1
SS14L EXT OR,D7,Diode_SMD:D_SOD-123F,C190475,SS14L,1
1.5A RESETTABLE,F1,Fuse:Fuse_1206_3216Metric_Pad1.42x1.75mm_HandSolder,,1206L150,1
600R@100MHz 1A,"FB1,FB2,FB3,FB4",Inductor_SMD:L_0805_2012Metric_Pad1.05x1.20mm_HandSolder,,BLM21PG601SN1D,4
3.9uH >=3A,L1,Inductor_SMD:L_Changjiang_FNR6020S,,FNR6020S-3R9M,1
22R 1%,"R10,R9",Resistor_SMD:R_0805_2012Metric,,,2
10k,"R11,R14,R33,R34,R35,R37,R38,R39,R40,R41",Resistor_SMD:R_0805_2012Metric_Pad1.20x1.40mm_HandSolder,,,10
8k25 1%,R12,Resistor_SMD:R_0805_2012Metric_Pad1.20x1.40mm_HandSolder,,,1
4k99 1%,R13,Resistor_SMD:R_0805_2012Metric_Pad1.20x1.40mm_HandSolder,,,1
33R,"R15,R16",Resistor_SMD:R_0805_2012Metric_Pad1.20x1.40mm_HandSolder,,,2
78R7 0.1%,"R2,R4",Aster_Production:Resistor_SMD__R_0805_2012Metric_Pad1.20x1.40mm_HandSolder__AsterProd,,,2
0R,R3,Resistor_SMD:R_0805_2012Metric_Pad1.20x1.40mm_HandSolder,,,1
1k,"R36,R42,R43,R44,R45",Resistor_SMD:R_0805_2012Metric_Pad1.20x1.40mm_HandSolder,,,5
324R 0.1%,R46,Aster_Production:Resistor_SMD__R_0805_2012Metric_Pad1.20x1.40mm_HandSolder__AsterProd,,,1
402R 0.1%,R47,Aster_Production:Resistor_SMD__R_0805_2012Metric_Pad1.20x1.40mm_HandSolder__AsterProd,,,1
3k92 0.1%,R5,Aster_Production:Resistor_SMD__R_0805_2012Metric_Pad1.20x1.40mm_HandSolder__AsterProd,,,1
4k00 0.1%,R6,Resistor_SMD:R_0805_2012Metric_Pad1.20x1.40mm_HandSolder,,,1
2k00 0.1%,"R7,R8",Resistor_SMD:R_0805_2012Metric_Pad1.20x1.40mm_HandSolder,,,2
33R x4 isolated,"RN1,RN2,RN3,RN4",Resistor_SMD:R_Array_Convex_4x0603,C102663,RTA03-4D330JTP,4
10M16SAE144C8G,U1,Package_QFP:EQFP-144-1EP_20x20mm_P0.5mm_EP4x4mm,C1521931,10M16SAE144C8G,1
ADS5560IRGZT,U2,Package_DFN_QFN:Texas_RGZ0048A_VQFN-48-1EP_7x7mm_P0.5mm_EP5.15x5.15mm,C571255,ADS5560IRGZT,1
THS4551IDGKT,U3,Package_SO:VSSOP-8_3x3mm_P0.65mm,C2860660,THS4551IDGKT,1
AP63203WU-7,U4,Package_TO_SOT_SMD:TSOT-23-6_HandSoldering,C780769,AP63203WU-7,1
40.000 MHz CMOS,Y1,Oscillator:Oscillator_SMD_Abracon_ASE-4Pin_3.2x2.5mm_HandSoldering,C1670009,ASE-40.000MHZ-L-C-T,1

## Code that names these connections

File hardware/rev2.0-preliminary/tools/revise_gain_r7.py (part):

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    sheet_marker = text.index("(embedded_fonts no)")
    switch_labels = "".join(
        [
            label("GAIN_H_SIG", 29.21, 71.12, "sw1-1"),
            label("GAIN_M_SIG", 29.21, 73.66, "sw1-2"),
            label("GAIN_SRC", 29.21, 76.2, "sw1-3"),
            label("GAIN_L_SIG", 29.21, 78.74, "sw1-4"),
            label("GAIN_H_GND", 29.21, 81.28, "sw1-5"),
            label("GAIN_M_GND", 29.21, 83.82, "sw1-6"),
            label("GND", 29.21, 86.36, "sw1-7"),
            label("GAIN_L_GND", 29.21, 88.9, "sw1-8"),
            label("GAIN_M_SIG", 191.77, 285.75, "r46-1"),
            label("FDA_INN", 191.77, 288.29, "r46-2"),
            label("GAIN_M_GND", 220.98, 285.75, "r47-1"),
            label("FDA_INP", 220.98, 288.29, "r47-2"),
        ]
    )
    new_symbols = resistor_instance("R46", "324R 0.1%", 207.01, 287.02)
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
